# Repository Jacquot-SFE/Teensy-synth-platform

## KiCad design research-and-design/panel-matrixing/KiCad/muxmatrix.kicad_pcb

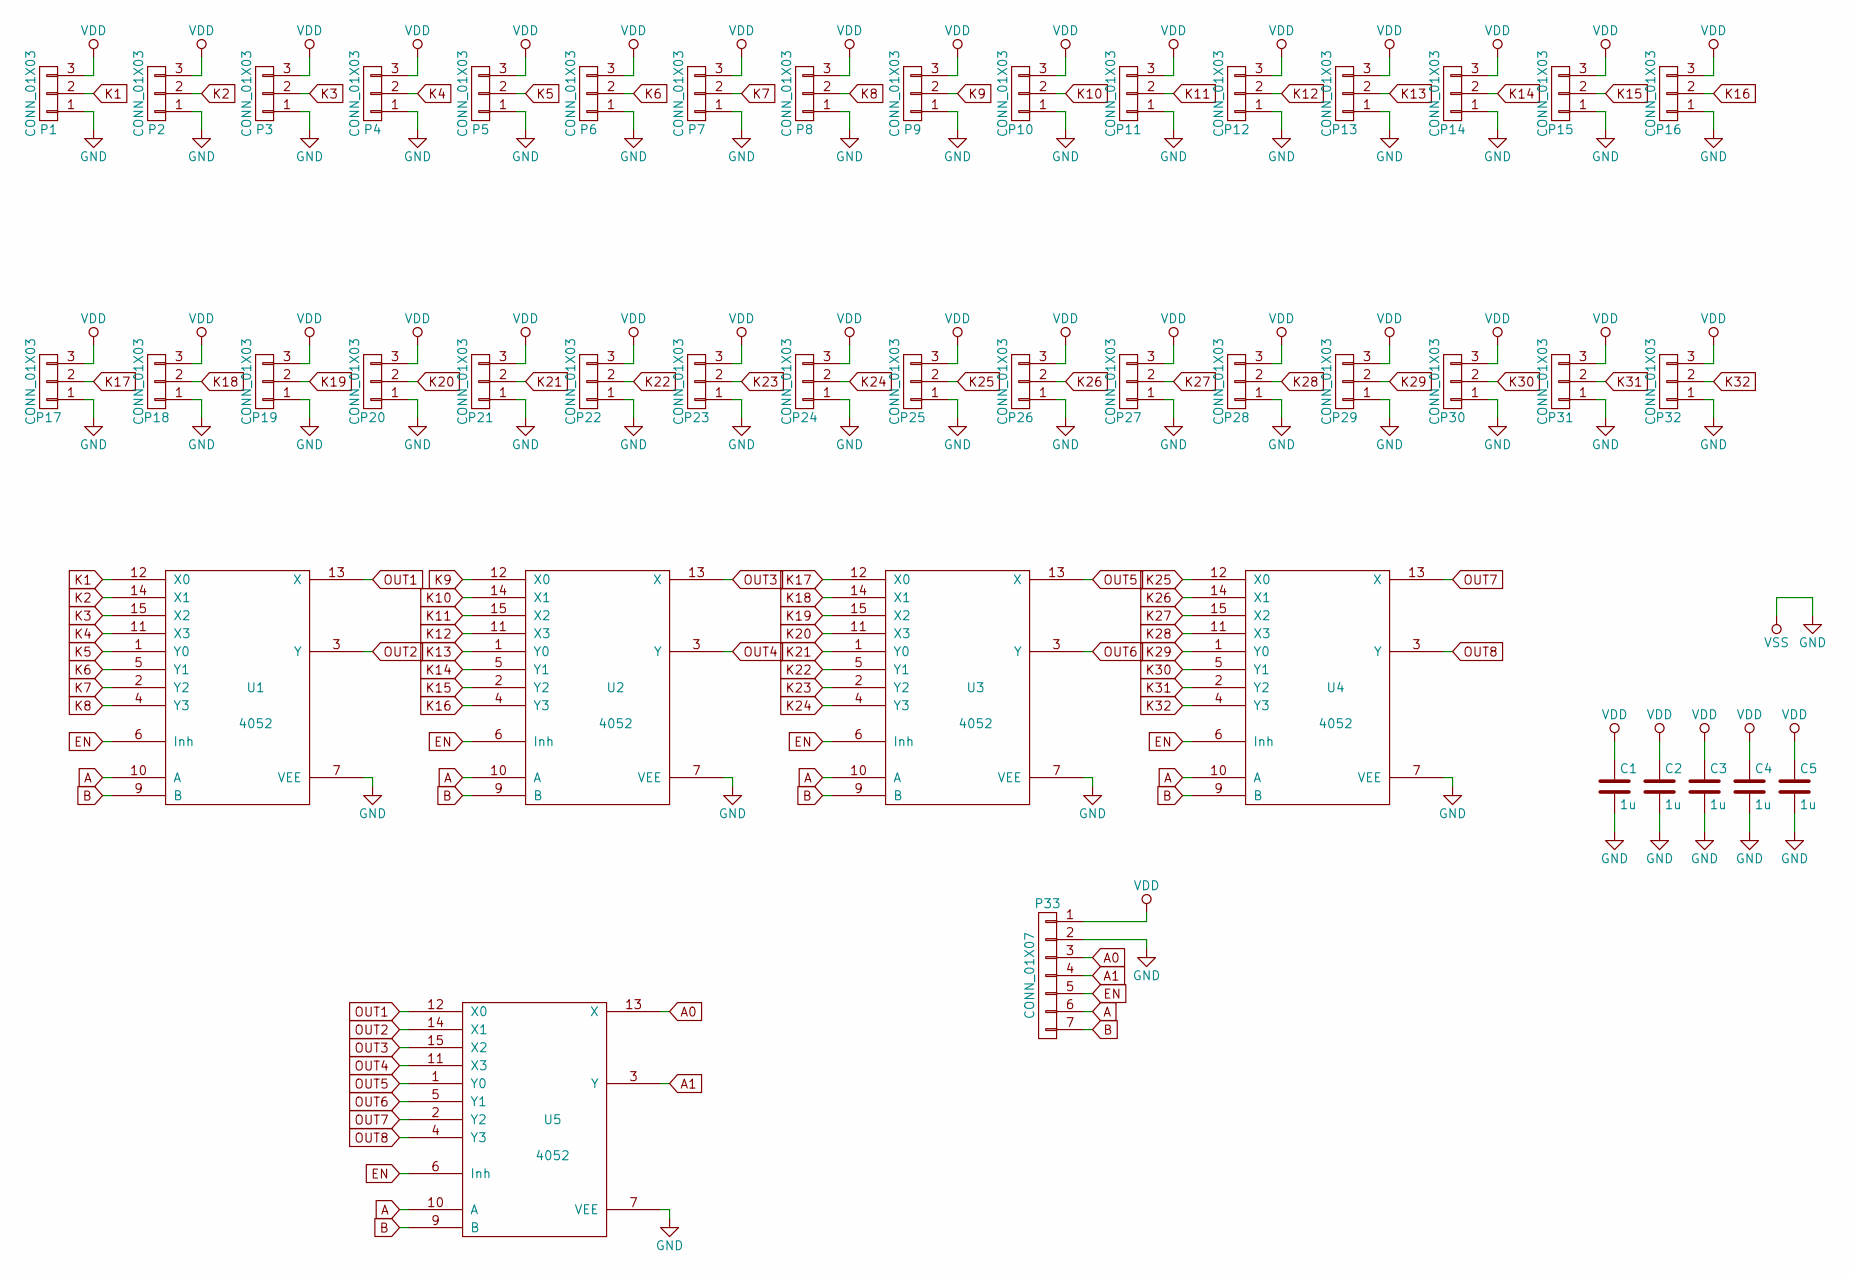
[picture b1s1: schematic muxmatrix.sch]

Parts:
C1, C2, C3, C4, C5: 1u; C_0603
P1, P2, P3, P4, P5, P6, P7, P8, P9, P10, P11, P12, P13, P14, P15, P16, P17, P18, P19, P20, P21, P22, P23, P24, P25, P26, P27, P28, P29, P30, P31, P32: CONN_01X03; dualpot
P33: CONN_01X07; Pin_Header_Straight_1x07
U1, U2, U3, U4, U5: 4052; SO-16-N

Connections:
A: P33.6, U1.10 (A), U2.10 (A), U3.10 (A), U4.10 (A), U5.10 (A)
A0: P33.3, U5.13 (X)
A1: P33.4, U5.3 (Y)
B: P33.7, U1.9 (B), U2.9 (B), U3.9 (B), U4.9 (B), U5.9 (B)
EN: P33.5, U1.6 (Inh), U2.6 (Inh), U3.6 (Inh), U4.6 (Inh), U5.6 (Inh)
GND: C1.2, C2.2, C3.2, C4.2, C5.2, P1.1, P2.1, P3.1, P4.1, P5.1, P6.1, P7.1, P8.1, P9.1, P10.1, P11.1, P12.1, P13.1, P14.1, P15.1, P16.1, P17.1, P18.1, P19.1, P20.1, P21.1, P22.1, P23.1, P24.1, P25.1, P26.1, P27.1, P28.1, P29.1, P30.1, P31.1, P32.1, P33.2, U1.7 (VEE), U1.8 (VSS), U2.7 (VEE), U2.8 (VSS), U3.7 (VEE), U3.8 (VSS), U4.7 (VEE), U4.8 (VSS), U5.7 (VEE), U5.8 (VSS)
K1: P1.2, U1.12 (X0)
K2: P2.2, U1.14 (X1)
K3: P3.2, U1.15 (X2)
K4: P4.2, U1.11 (X3)
K5: P5.2, U1.1 (Y0)
K6: P6.2, U1.5 (Y1)
K7: P7.2, U1.2 (Y2)
K8: P8.2, U1.4 (Y3)
K9: P9.2, U2.12 (X0)
K10: P10.2, U2.14 (X1)
K11: P11.2, U2.15 (X2)
K12: P12.2, U2.11 (X3)
K13: P13.2, U2.1 (Y0)
K14: P14.2, U2.5 (Y1)
K15: P15.2, U2.2 (Y2)
K16: P16.2, U2.4 (Y3)
K17: P17.2, U3.12 (X0)
K18: P18.2, U3.14 (X1)
K19: P19.2, U3.15 (X2)
K20: P20.2, U3.11 (X3)
K21: P21.2, U3.1 (Y0)
K22: P22.2, U3.5 (Y1)
K23: P23.2, U3.2 (Y2)
K24: P24.2, U3.4 (Y3)
K25: P25.2, U4.12 (X0)
K26: P26.2, U4.14 (X1)
K27: P27.2, U4.15 (X2)
K28: P28.2, U4.11 (X3)
K29: P29.2, U4.1 (Y0)
K30: P30.2, U4.5 (Y1)
K31: P31.2, U4.2 (Y2)
K32: P32.2, U4.4 (Y3)
OUT1: U1.13 (X), U5.12 (X0)
OUT2: U1.3 (Y), U5.14 (X1)
OUT3: U2.13 (X), U5.15 (X2)
OUT4: U2.3 (Y), U5.11 (X3)
OUT5: U3.13 (X), U5.1 (Y0)
OUT6: U3.3 (Y), U5.5 (Y1)
OUT7: U4.13 (X), U5.2 (Y2)
OUT8: U4.3 (Y), U5.4 (Y3)
VDD: C1.1, C2.1, C3.1, C4.1, C5.1, P1.3, P2.3, P3.3, P4.3, P5.3, P6.3, P7.3, P8.3, P9.3, P10.3, P11.3, P12.3, P13.3, P14.3, P15.3, P16.3, P17.3, P18.3, P19.3, P20.3, P21.3, P22.3, P23.3, P24.3, P25.3, P26.3, P27.3, P28.3, P29.3, P30.3, P31.3, P32.3, P33.1, U1.16 (VDD), U2.16 (VDD), U3.16 (VDD), U4.16 (VDD), U5.16 (VDD)

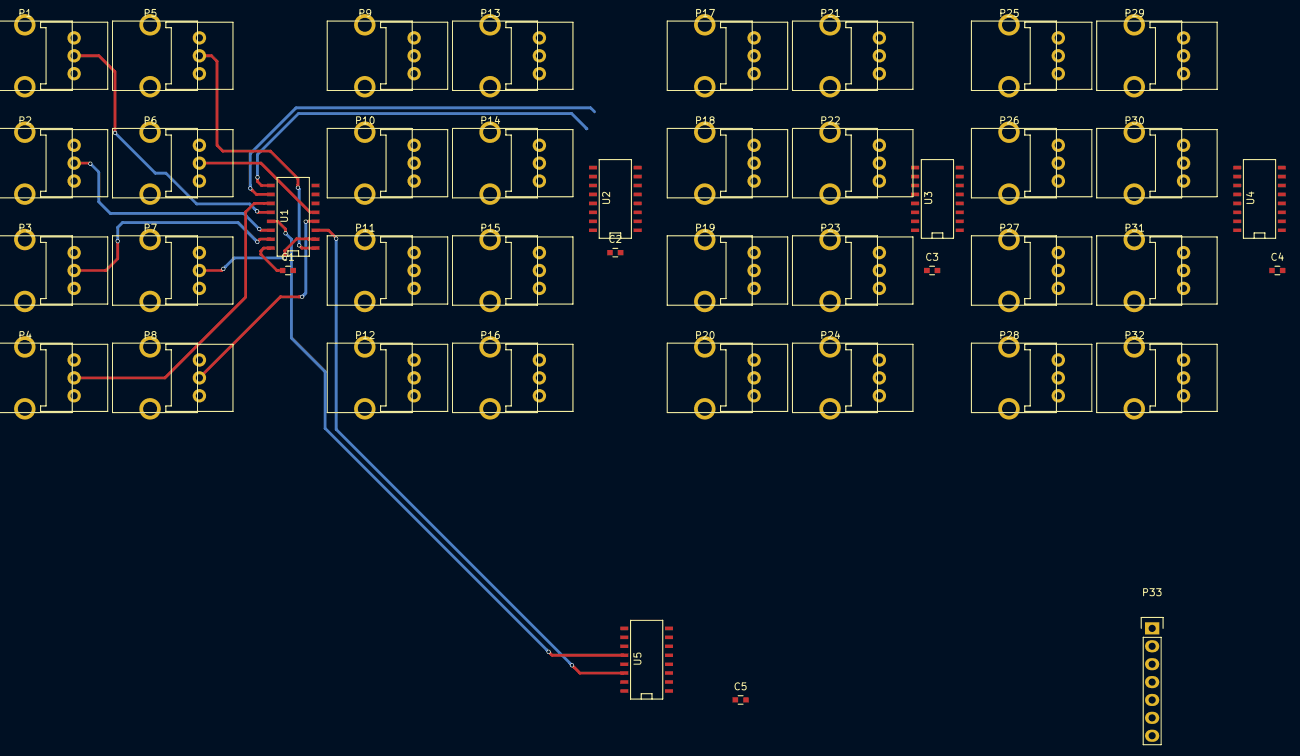
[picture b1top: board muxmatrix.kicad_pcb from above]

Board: 2 copper layers, 43 parts (0 on the bottom side), 47 nets.

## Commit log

2015-12-09 :tada: Added .gitattributes & .gitignore files
2015-12-09 Adding a first stab at docs.
2015-12-09 Added Form Factor bullet
2015-12-11 added some multiplexing research
2015-12-11 did some power supply research
2015-12-14 added basic transformer simulation
2015-12-14 Added discrete flyback simulation
2015-12-14 deleted lock
2015-12-16 Added decode summer to options and topology
2015-12-18 updated topology and created kicad project
2015-12-19 worked on layout
2015-12-28 Adding concept spec for Teensy-boom
2015-12-28 Some small updates, seeing the MD rendered for real
2015-12-30 Testing out new dual trimpot footprint
2016-01-03 removed kicad project
2016-01-09 Getting more complete .gitignore
2016-01-09 Another update to .gitignore, and boom initial files.
2016-01-09 Adding sgtl5000 to library.
    Need to doublecheck the TX/RX pins. Is the terminilogy always in
    reference to the bus master?
2016-01-12 More PCB work
    Added knobs, buttons, connectors, MIDI.
    Basic PCB alignment in place...~6"x4"
2016-01-19 More work on PCB/Schem
2016-01-21 More work on BOOM schem/PCB.
2016-01-26 updated docs
2016-02-08 Checking in WIP of large Teensy-BOOM board, so I can move to smaller one.
2016-02-10 Adding teensy-boom Junior board.
2016-02-10 Small updates to get ready to fab.
2016-02-21 Added FreeCAD parts for first cheeks
2016-02-21 generated toolpaths
2016-02-21 adjusted margins
2016-02-22 photographed the testbed
2016-02-26 Starting presentation slide deck.
2016-02-26 Slide updates.
2016-02-29 Small slide updates
    Making sure the presentation runs on my laptop.
2016-03-02 worked on documentation
2016-03-03 Bunch of updates to slide deck.
2016-03-03 Added HW details
2016-03-04 One last touchup to slide deck.
2016-03-04 moved images
